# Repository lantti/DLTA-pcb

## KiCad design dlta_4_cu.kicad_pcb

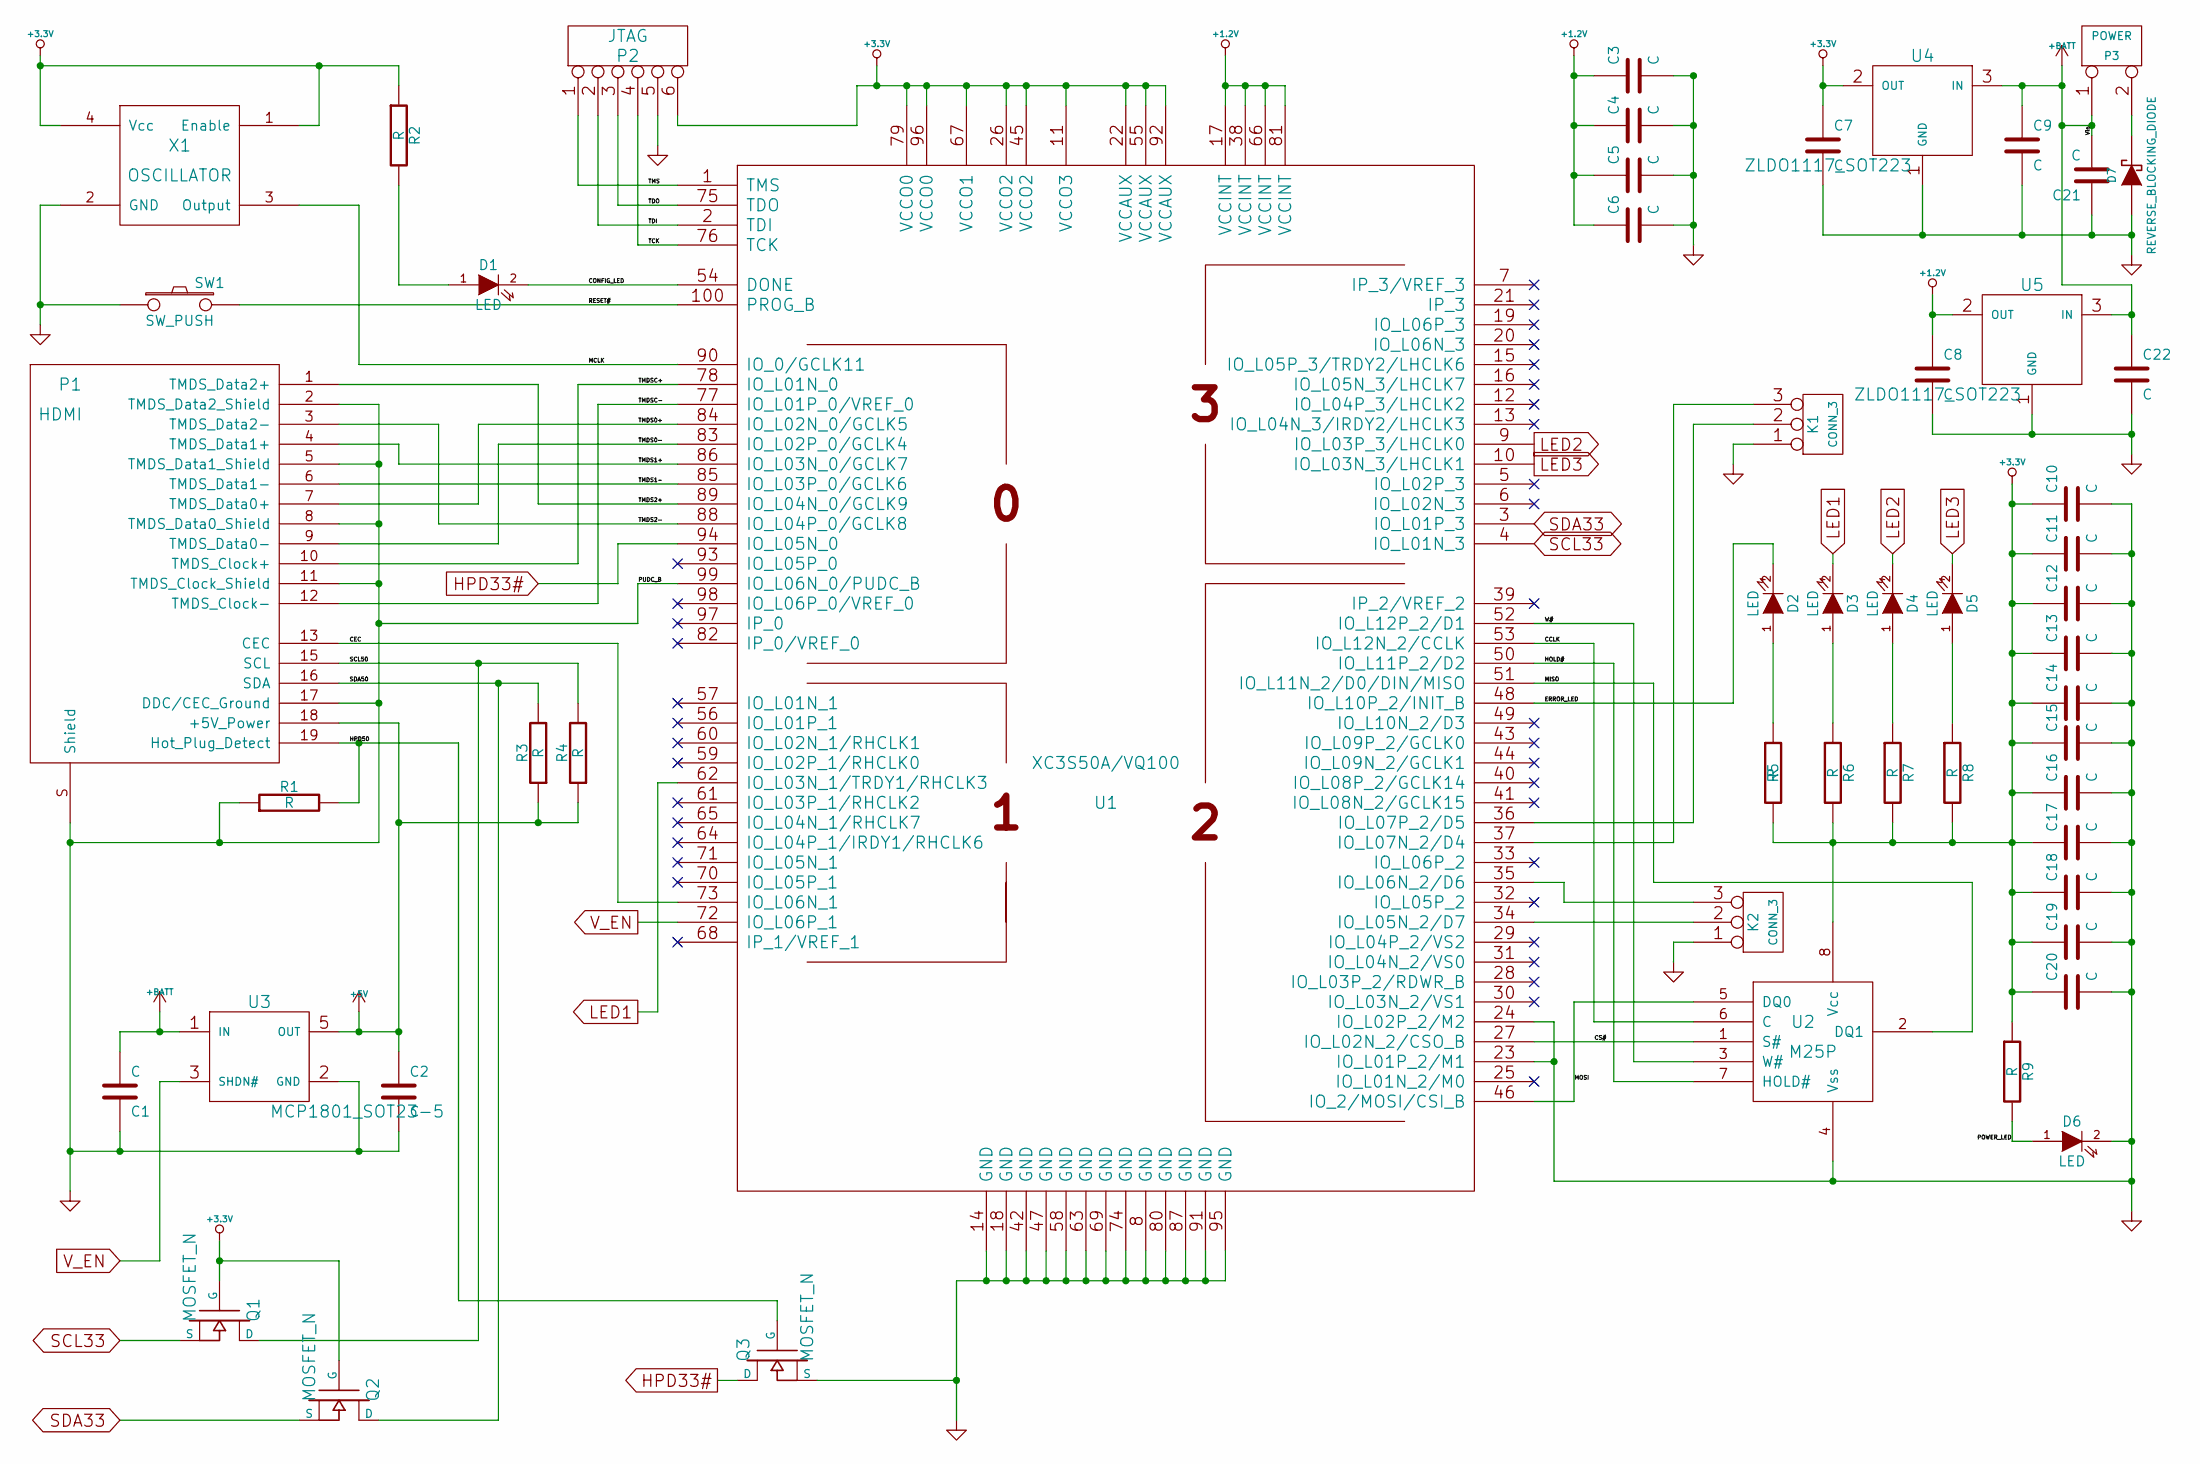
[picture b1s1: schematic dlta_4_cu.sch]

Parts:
C1, C2, C3, C4, C5, C6, C7, C8, C9, C10, C11, C12, C13, C14, C15, C16, C17, C18, C19, C20, C22: C; c_0603_Handsoldering
C21: C; Resistor_SMD1206_HandSoldering
D1, D2, D3, D4, D5, D6: LED; LED-0805
D7: REVERSE_BLOCKING_DIODE; Resistor_SMD1206_HandSoldering
K1, K2: CONN_3; Pin_Header_Straight_1x03
P1: HDMI; HDMI_A_RECEPTACLE
P2: JTAG; Pin_Header_Straight_1x06
P3: POWER; Pin_Header_Straight_1x02
Q1, Q2, Q3: MOSFET_N; SOT23_bigger_pads
R1, R2, R3, R4, R5, R6, R7, R8, R9: R; Resistor_SMD0805_HandSoldering
SW1: SW_PUSH; FSMSM
U1: XC3S50A/VQ100; VQFP100_long_pads_mm_pitch
U2: M25P; SO8W
U3: MCP1801_SOT23-5; SOT23-5_Handsoldering
U4, U5: ZLDO1117_SOT223; SOT223_Handsoldering
X1: OSCILLATOR; 5mmx7mm_OSC

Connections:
+1.2V: C3.1, C4.1, C5.1, C6.1, C8.1, U1.17 (VCCINT), U1.38 (VCCINT), U1.66 (VCCINT), U1.81 (VCCINT), U5.2 (OUT)
+3.3V: C7.1, C10.1, C11.1, C12.1, C13.1, C14.1, C15.1, C16.1, C17.1, C18.1, C19.1, C20.1, P2.6, Q1.G, Q2.G, R2.1, R5.2, R6.2, R7.2, R8.2, R9.1, U1.11 (VCCO3), U1.22 (VCCAUX), U1.26 (VCCO2), U1.45 (VCCO2), U1.55 (VCCAUX), U1.67 (VCCO1), U1.79 (VCCO0), U1.92 (VCCAUX), U1.96 (VCCO0), U2.8 (Vcc), U4.2 (OUT), X1.1 (Enable), X1.4 (Vcc)
+5V: C2.1, P1.18 (+5V_Power), R3.1, R4.1, U3.5 (OUT)
+BATT: C1.2, C9.1, C21.2, C22.1, P3.1, U3.1 (IN), U4.3 (IN), U5.3 (IN)
/CCLK: U1.53 (IO_L12N_2/CCLK), U2.6 (C)
/CEC: P1.13 (CEC), U1.73 (IO_L06N_1)
/CONFIG_LED: D1.2 (K), U1.54 (DONE)
/CS#: U1.27 (IO_L02N_2/CSO_B), U2.1 (S#)
/ERROR_LED: D2.2 (K), U1.48 (IO_L10P_2/INIT_B)
/HOLD#: U1.50 (IO_L11P_2/D2), U2.7 (HOLD#)
/HPD50: P1.19 (Hot_Plug_Detect), Q3.G, R1.2
/MCLK: U1.90 (IO_0/GCLK11), X1.3 (Output)
/MISO: U1.51 (IO_L11N_2/D0/DIN/MISO), U2.2 (DQ1)
/MOSI: U1.46 (IO_2/MOSI/CSI_B), U2.5 (DQ0)
/POWER_LED: D6.1 (A), R9.2
/RESET#: SW1.2, U1.100 (PROG_B)
/SCL50: P1.15 (SCL), Q1.D, R4.2
/SDA50: P1.16 (SDA), Q2.D, R3.2
/TCK: P2.4, U1.76 (TCK)
/TDI: P2.2, U1.2 (TDI)
/TDO: P2.3, U1.75 (TDO)
/TMDS0+: P1.7 (TMDS_Data0+), U1.84 (IO_L02N_0/GCLK5)
/TMDS0-: P1.9 (TMDS_Data0-), U1.83 (IO_L02P_0/GCLK4)
/TMDS1+: P1.4 (TMDS_Data1+), U1.86 (IO_L03N_0/GCLK7)
/TMDS1-: P1.6 (TMDS_Data1-), U1.85 (IO_L03P_0/GCLK6)
/TMDS2+: P1.1 (TMDS_Data2+), U1.89 (IO_L04N_0/GCLK9)
/TMDS2-: P1.3 (TMDS_Data2-), U1.88 (IO_L04P_0/GCLK8)
/TMDSC+: P1.10 (TMDS_Clock+), U1.78 (IO_L01N_0)
/TMDSC-: P1.12 (TMDS_Clock-), U1.77 (IO_L01P_0/VREF_0)
/TMS: P2.1, U1.1 (TMS)
/W#: U1.52 (IO_L12P_2/D1), U2.3 (W#)
GND: C1.1, C2.2, C3.2, C4.2, C5.2, C6.2, C7.2, C8.2, C9.2, C10.2, C11.2, C12.2, C13.2, C14.2, C15.2, C16.2, C17.2, C18.2, C19.2, C20.2, C21.1, C22.2, D6.2 (K), D7.1 (A), K1.1, K2.1, P1.2 (TMDS_Data2_Shield), P1.5 (TMDS_Data1_Shield), P1.8 (TMDS_Data0_Shield), P1.11 (TMDS_Clock_Shield), P1.17 (DDC/CEC_Ground), P1.S (Shield), P2.5, Q3.S, R1.1, SW1.1, U1.8 (GND), U1.14 (GND), U1.18 (GND), U1.23 (IO_L01P_2/M1), U1.24 (IO_L02P_2/M2), U1.42 (GND), U1.47 (GND), U1.58 (GND), U1.63 (GND), U1.69 (GND), U1.74 (GND), U1.80 (GND), U1.87 (GND), U1.91 (GND), U1.95 (GND), U1.99 (IO_L06N_0/PUDC_B), U2.4 (Vss), U3.2 (GND), U4.1 (GND), U5.1 (GND), X1.2 (GND)
HPD33#: Q3.D, U1.94 (IO_L05N_0)
LED1: D3.2 (K), U1.62 (IO_L03N_1/TRDY1/RHCLK3)
LED2: D4.2 (K), U1.9 (IO_L03P_3/LHCLK0)
LED3: D5.2 (K), U1.10 (IO_L03N_3/LHCLK1)
unnamed: D1.1 (A), R2.2
unnamed: D2.1 (A), R5.1
unnamed: D3.1 (A), R6.1
unnamed: D4.1 (A), R7.1
unnamed: D5.1 (A), R8.1
unnamed: D7.2 (K), P3.2 (PM)
unnamed: K1.2 (PM), U1.36 (IO_L07P_2/D5)
unnamed: K1.3, U1.37 (IO_L07N_2/D4)
unnamed: K2.2 (PM), U1.34 (IO_L05N_2/D7)
unnamed: K2.3, U1.35 (IO_L06N_2/D6)
SCL33: Q1.S, U1.4 (IO_L01N_3)
SDA33: Q2.S, U1.3 (IO_L01P_3)
V_EN: U1.72 (IO_L06P_1), U3.3 (SHDN#)

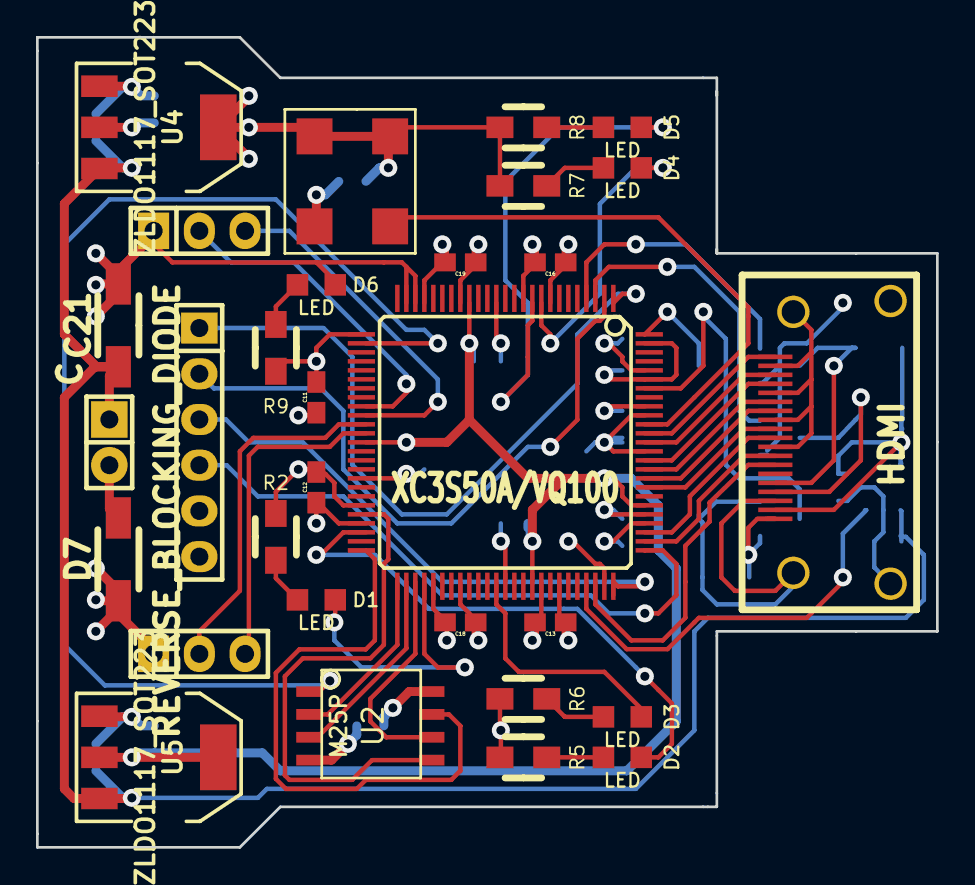
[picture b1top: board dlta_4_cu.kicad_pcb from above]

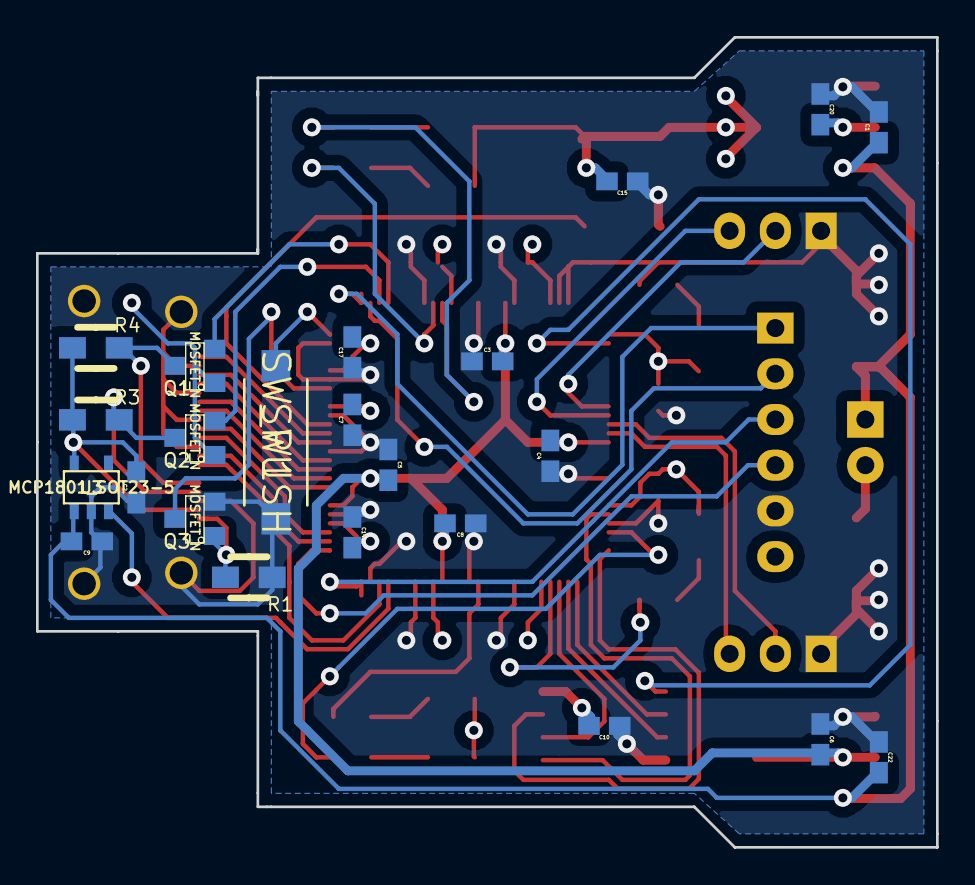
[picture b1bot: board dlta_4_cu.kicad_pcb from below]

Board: 4 copper layers, 50.0 x 45.0 mm, 53 parts (23 on the bottom side), 49 nets.

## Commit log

2016-07-03 lets put dlta pcb on git too
